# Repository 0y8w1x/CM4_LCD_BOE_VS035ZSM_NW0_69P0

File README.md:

# CM4_LCD_BOE_VS035ZSM_NW0_69P0
Raspberry Pi CM4 bindings for BOE VS035ZSM-NW0-69P0 1440x1600 LCD display

**NOTE:** Large parts are copied from the [JDI LT070ME05000](https://github.com/harlab/CM4_LCD_LT070ME05000) LCD

**Status:** Should work, but due to chip shortage not tested yet.

# Overview
BOE VS035ZSM NW0 69P0 panel is a 1440x1600 4-lane DSI LCD display. To use it, 4-lane DSI interface is required, so it can be used with Raspberry Pi Compute Modules 3 and 4.

# Software installation
We need build rpi-5.10.y branch with BOE VS035ZSM NW0 69P0 panel module enabled. This is well documented at Raspberry Pi help pages [here](https://www.raspberrypi.org/documentation/linux/kernel/building.md) and [here](https://www.raspberrypi.org/documentation/linux/kernel/configuring.md)

NOTE: For cross-compiling, see information [here](https://www.raspberrypi.org/documentation/linux/kernel/building.md)

```
sudo apt install git bc bison flex libssl-dev make
sudo apt install libncurses5-dev
git clone --depth=1 --branch rpi-5.10.y https://github.com/raspberrypi/linux
```
Copy the files from THIS repository to the kernel and add it to the Make/Kconfig files for it to build.
```
cp panel-boe-vs035zsm-nw0-69p0.c linux/drivers/gpu/drm/panel/panel-boe-vs035zsm-nw0-69p0.c
cp vc4-kms-dsi-vs035zsm-nw0-69p0-overlay.dts linux/arch/arm/boot/dts/overlays/vc4-kms-dsi-vs035zsm-nw0-69p0-overlay.dts
```

Add an entry to linux/drivers/gpu/drm/panel/Kconfig

Add an entry to linux/drivers/gpu/drm/panel/Makefile

Add an entry to linux/arch/arm/boot/dts/overlays/README

Add an entry to linux/arch/arm/boot/dts/overlays/Makefile

```
cd linux
KERNEL=kernel7l
make bcm2711_defconfig
make menuconfig
```

Navigate to Device Drivers/Graphics support/Display panel, check BOE VS035ZSM NW0 69P0 panel and save

Now we need to build and install kernel:
```
make -j4 zImage modules dtbs
sudo make modules_install
sudo cp arch/arm/boot/dts/*.dtb /boot/
sudo cp arch/arm/boot/dts/overlays/*.dtb* /boot/overlays/
sudo cp arch/arm/boot/dts/overlays/README /boot/overlays/
sudo cp arch/arm/boot/zImage /boot/$KERNEL.img
```

Then compile and copy the Device Tree source to boot partition:
```
sudo dtc -@ -I dts -O dtb -o vc4-kms-dsi-vs035zsm-nw0-69p0.dtbo vc4-kms-dsi-vs035zsm-nw0-69p0-overlay.dts
sudo cp vc4-kms-dsi-vs035zsm-nw0-69p0.dtbo /boot/overlays/
```

Then edit /boot/config.txt to add:
```
ignore_lcd=1
dtoverlay=vc4-kms-v3d
dtoverlay=vc4-kms-dsi-vs035zsm-nw0-69p0
```
and reboot

After reboot screen should we working and have portrait orientation. To adjust, use Main Menu/Preferences/Screen configuration utility

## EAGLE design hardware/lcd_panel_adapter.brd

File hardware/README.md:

**Note:** The board and schematic files are for Autodesk EAGLE.

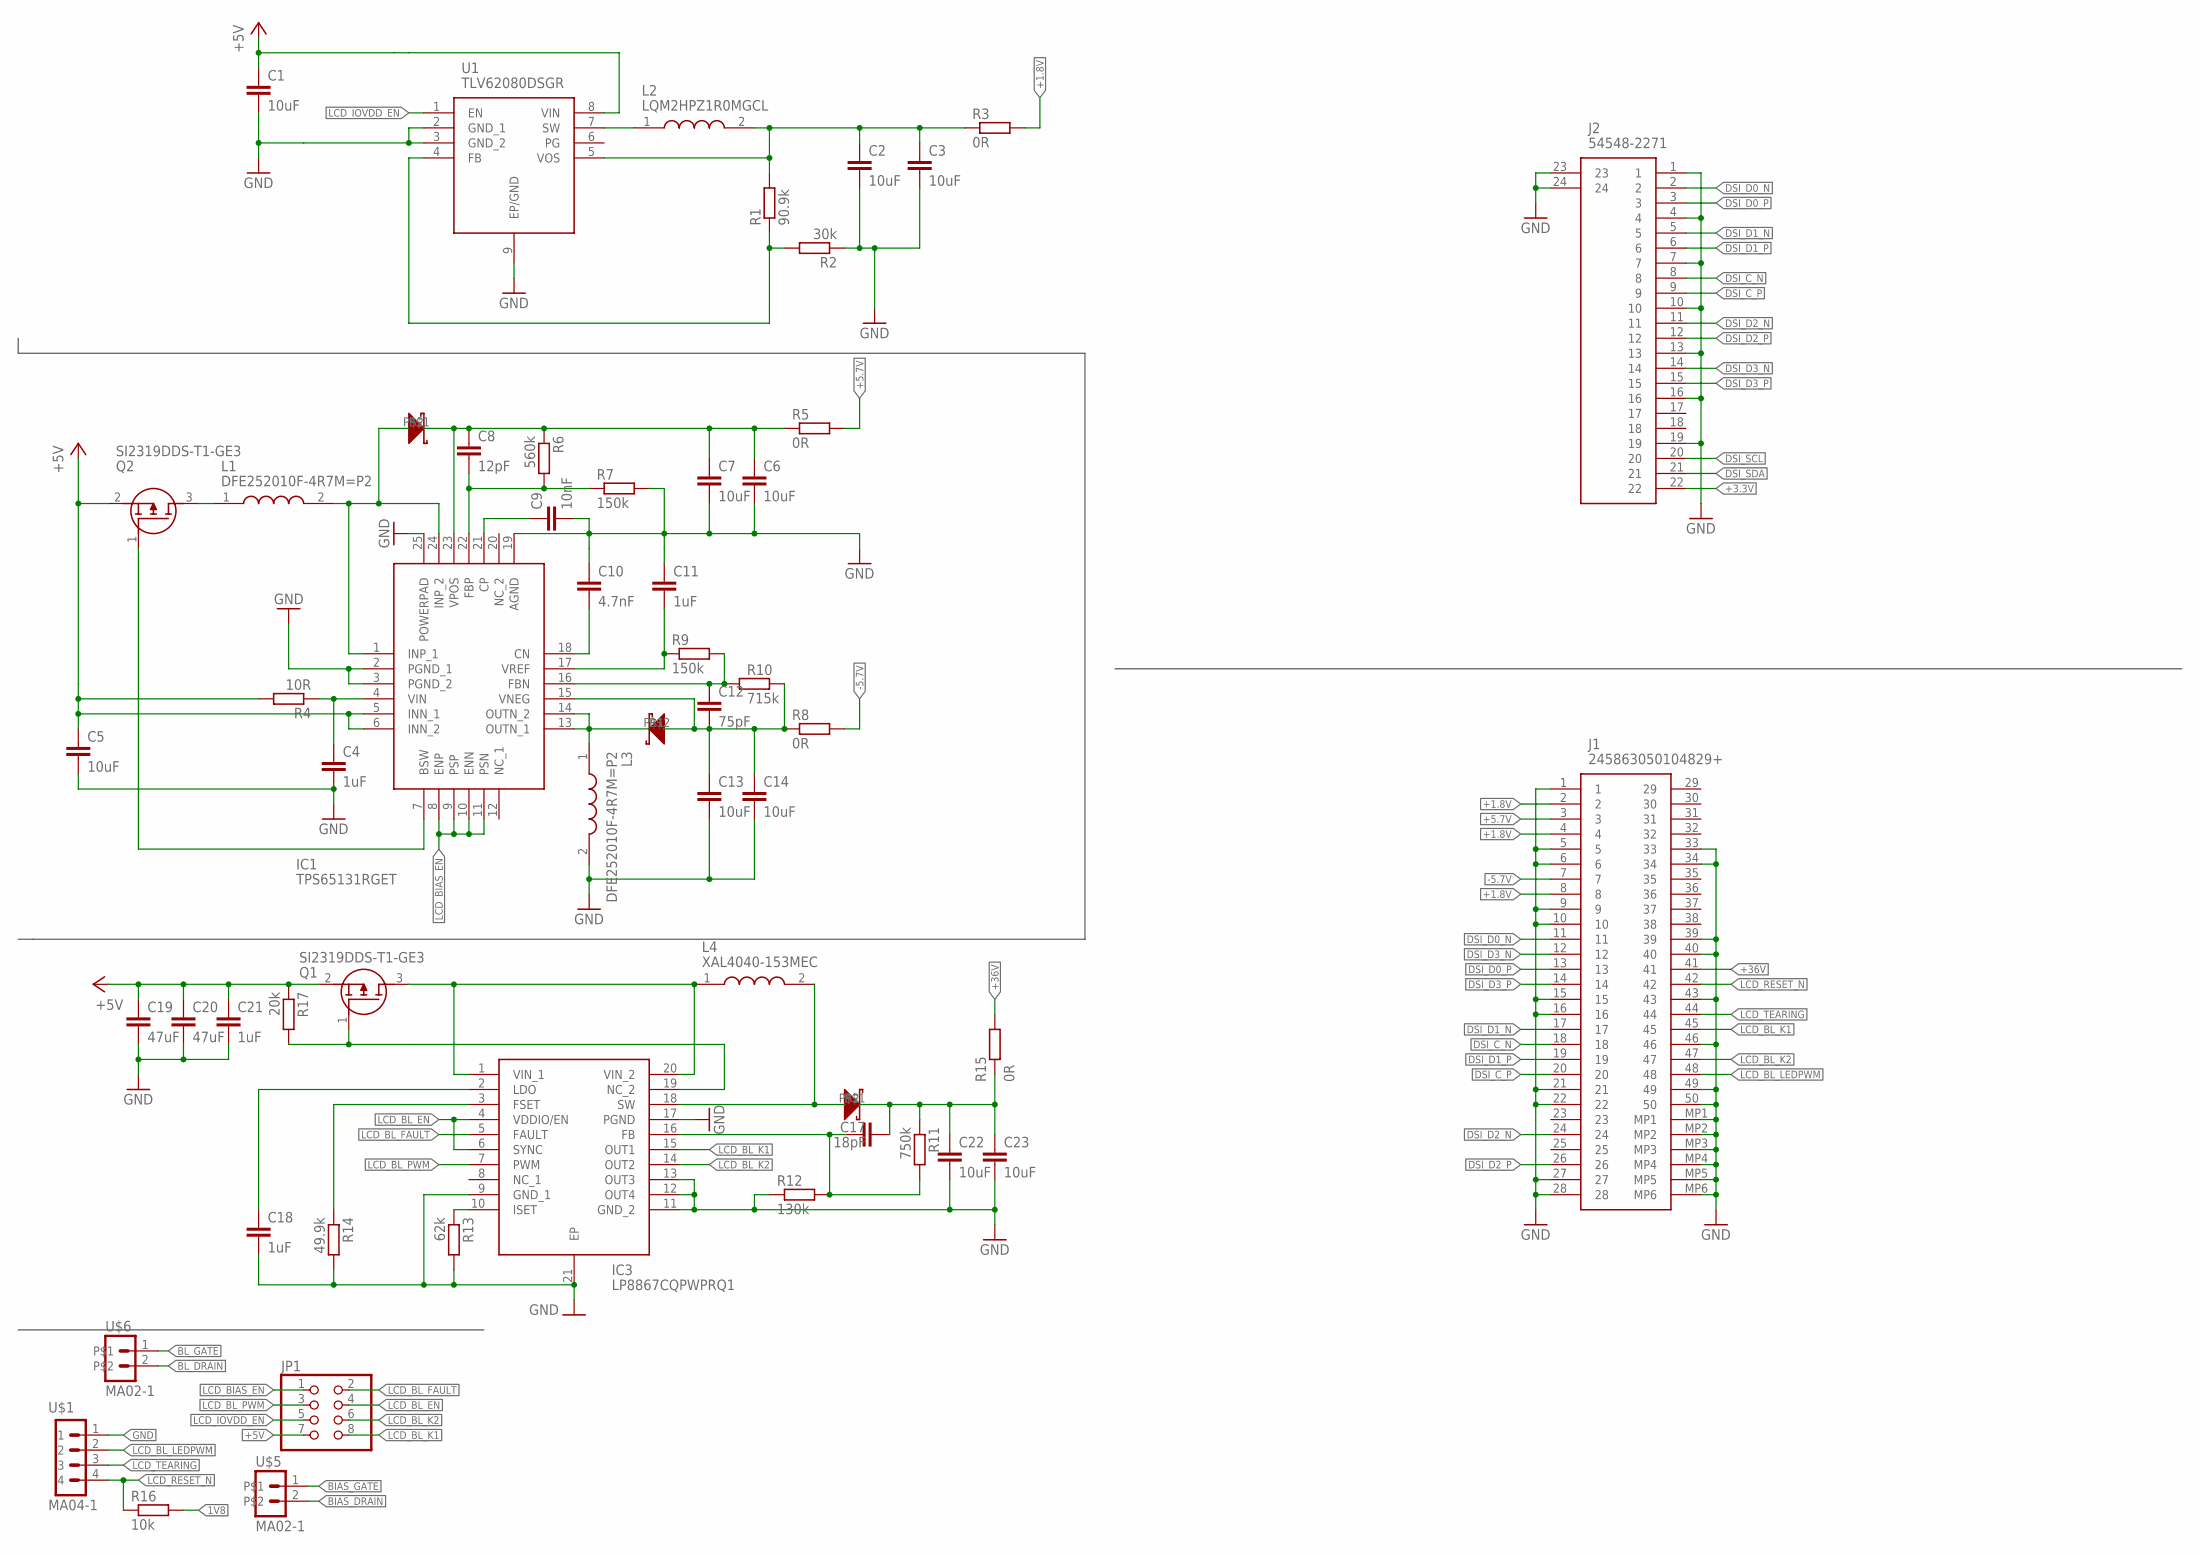
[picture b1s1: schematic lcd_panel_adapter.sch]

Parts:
C1, C2, C3, C5, C6, C7, C13, C14: 10uF; C0603
C4, C11, C18, C21: 1uF; C0603
C8: 12pF; C0603
C9: 10nF; C0603
C10: 4.7nF; C0603
C12: 75pF; C0603
C17: 18pF; C0603
C19, C20: 47uF; C0603
C22, C23: 10uF; C1206
IC1: TPS65131RGET; QFN50P400X400X100-25N
IC3: LP8867CQPWPRQ1; SOP65P640X120-21N
J1: 245863050104829+; 245863050104829
J2: 54548-2271; 545482271
JP1: PINHD-2X4; 2X04
L1, L3: DFE252010F-4R7M=P2; 1269ASH100NP2
L2: LQM2HPZ1R0MGCL; LQM2HPN1R0MG0L
L4: XAL4040-153MEC; XAL4040153MEC
Q1, Q2: SI2319DDS-T1-GE3; SOT96P240X120-3N
R1: 90.9k; R0603
R2: 30k; R0603
R3, R5, R8, R15: 0R; R0603
R4: 10R; R0603
R6: 560k; R0603
R7, R9: 150k; R0603
R10: 715k; R0603
R11: 750k; R0603
R12: 130k; R0603
R13: 62k; R0603
R14: 49.9k; R0603
R16: 10k; R0603
R17: 20k; R0603
U1: TLV62080DSGR; SON50P200X200X80-9N
U$1: MA04-1
U$2, U$3, U$4: CUS10S40
U$5, U$6: MA02-1

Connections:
1V8: C2.1, C3.1, L2.2, R1.2, R3.1, R16.2, U1.5 (VOS)
+1.8V: J1.2, J1.4, J1.8, R3.2
+3.3V: J2.22
+5.7V: J1.3, R5.2
+5V: C1.1, C5.1, C19.1, C20.1, C21.1, IC1.5 (INN_1), IC1.6 (INN_2), JP1.7, Q1.2 (S), Q2.2 (S), R4.2, R17.1, U1.8 (VIN)
+36V: J1.41, R15.2
-5.7V: J1.7, R8.2
BIAS_DRAIN: L1.1, Q2.3 (D), U$5.2
BIAS_GATE: IC1.7 (BSW), Q2.1 (G), U$5.1
BL_DRAIN: IC3.1 (VIN_1), IC3.20 (VIN_2), L4.1, Q1.3 (D), U$6.2
BL_GATE: IC3.19 (NC_2), Q1.1 (G), R17.2, U$6.1
DSI_C_N: J1.18, J2.8
DSI_C_P: J1.20, J2.9
DSI_D0_N: J1.11, J2.2
DSI_D0_P: J1.13, J2.3
DSI_D1_N: J1.17, J2.5
DSI_D1_P: J1.19, J2.6
DSI_D2_N: J1.24, J2.11
DSI_D2_P: J1.26, J2.12
DSI_D3_N: J1.12, J2.14
DSI_D3_P: J1.14, J2.15
DSI_SCL: J2.20
DSI_SDA: J2.21
FB: R1.1, R2.2, U1.4 (FB)
GND: C1.2, C2.2, C3.2, C4.2, C5.2, C6.2, C7.2, C9.2, C10.1, C11.1, C13.2, C14.2, C18.2, C19.2, C20.2, C21.2, C22.2, C23.2, IC1.2 (PGND_1), IC1.3 (PGND_2), IC1.19 (AGND), IC1.25 (POWERPAD), IC3.9 (GND_1), IC3.11 (GND_2), IC3.12 (OUT4), IC3.13 (OUT3), IC3.17 (PGND), IC3.21 (EP), J1.1, J1.5, J1.6, J1.9, J1.10, J1.15, J1.16, J1.21, J1.22, J1.27, J1.28, J1.33, J1.34, J1.39, J1.40, J1.43, J1.46, J1.49, J1.50, J1.MP1, J1.MP2, J1.MP3, J1.MP4, J1.MP5, J1.MP6, J2.1, J2.4, J2.7, J2.10, J2.13, J2.16, J2.19, J2.23, J2.24, L3.2, R2.1, R7.2, R12.1, R13.2, R14.2, U1.2 (GND_1), U1.3 (GND_2), U1.9 (EP/GND), U$1.1
LCD_BIAS_EN: IC1.8 (ENP), IC1.9 (PSP), IC1.10 (ENN), IC1.11 (PSN), JP1.1
LCD_BL_EN: IC3.4 (VDDIO/EN), IC3.6 (SYNC), JP1.4
LCD_BL_FAULT: IC3.5 (FAULT), JP1.2
LCD_BL_K1: IC3.15 (OUT1), J1.45, JP1.8
LCD_BL_K2: IC3.14 (OUT2), J1.47, JP1.6
LCD_BL_LEDPWM: J1.48, U$1.2
LCD_BL_PWM: IC3.7 (PWM), JP1.3
LCD_IOVDD_EN: JP1.5, U1.1 (EN)
LCD_RESET_N: J1.42, R16.1, U$1.4
LCD_TEARING: J1.44, U$1.3
unnamed: L2.1, U1.7 (SW)
unnamed: C4.1, IC1.4 (VIN), R4.1
unnamed: IC3.18 (SW), L4.2, U$4.P$1
unnamed: IC1.1 (INP_1), IC1.24 (INP_2), L1.2, U$2.P$1
unnamed: IC1.13 (OUTN_1), IC1.14 (OUTN_2), L3.1, U$3.P$2
unnamed: C6.1, C7.1, C8.1, IC1.23 (VPOS), R5.1, R6.1, U$2.P$2
unnamed: C9.1, IC1.21 (CP)
unnamed: C8.2, IC1.22 (FBP), R6.2, R7.1
unnamed: C12.2, C13.1, C14.1, IC1.15 (VNEG), R8.1, R10.2, U$3.P$1
unnamed: C11.2, IC1.17 (VREF), R9.1
unnamed: C10.2, IC1.18 (CN)
unnamed: C12.1, IC1.16 (FBN), R9.2, R10.1
unnamed: C17.1, IC3.16 (FB), R11.2, R12.2
unnamed: C18.1, IC3.2 (LDO)
unnamed: IC3.10 (ISET), R13.1
unnamed: IC3.3 (FSET), R14.1
NET_WHATEVER: C17.2, C22.1, C23.1, R11.1, R15.1, U$4.P$2

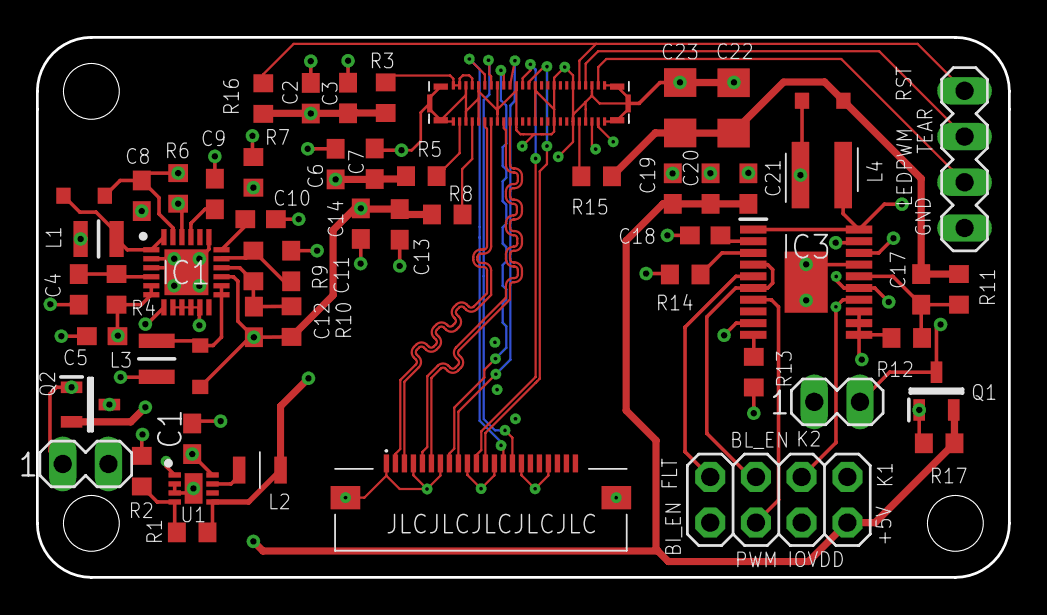
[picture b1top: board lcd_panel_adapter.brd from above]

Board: 4 copper layers, 54.0 x 30.0 mm, 56 parts (0 on the bottom side), 49 nets.

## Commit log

2021-07-04 explained what this repository is about
2021-07-04 added initial source files
2021-07-04 updated the Readme to reflect progress
2021-07-04 fixed dts syntax error
2021-07-04 credited the base code of the boe driver
2021-07-04 added instructions to build the driver
2021-07-04 formatted
2021-07-04 added raspberry pi boot config
2021-07-04 fixed typo
2021-07-04 added schematic, board file, and CAM data
2021-07-04 added readme for the hardware files
2021-07-04 updated the cam data
2021-07-04 deleted unnecessary files
2021-07-04 updated todo list
2021-07-04 created pdf for the board
2021-07-05 use kms instead of fkms
2021-07-05 changed gpio logic
2021-07-05 changed reset logic
2021-07-15 changed some gpio timings. It now works more reliable
2021-07-15 formatted the dts
2021-07-15 added +1.8V pullup resistor for LCD reset pin
2021-07-26 updated the backlight driver IC from LP8867 to TPS61194
2022-01-08 revert back from TPS61194 to LP8867, and add transistors
